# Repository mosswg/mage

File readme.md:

# Mage keyboard (V2 Coming Soon)

# Pictures (with kailh choc robins and MBK Legend Keycaps from [MKUltra Corporation](https://mkultra.click))

## Design principles
 - Resistor grid keyboards are annoying to design and build
 - Finger movement should be reduced as much as possible

## Inspiration
 - MiRage keyboard by Voidstar Labs (Zack Freedman): My motivation for making this
 - Ergodox: Control groups for thumbs
 - Lily58: The basis of the default layout

## Required Materials
 - Seeedstudio Xiao rp2040
 - x4 mcp23017 i/o expander
 - x4 3k Ohm 1204 SMD resistor
 - x4 10k Ohm 1204 SMD resistor
 - x2 3.5mm TRRS Jack
 - TRRS Cable
 - USB-C Cable
 - x64 kaihl choc v1 or v2 switch

## Build guide
1. Solder the R1 and R2 3kOhm resistors
2. Solder the R3 and R4 10kOhm resistors
3. Solder the I/O expanders
4. Solder the Xiao rp2040 on the left half
5. Solder the TRRS Jack
6. Solder on the switches
7. [Program the xiao with the firmware](#program-the-xiao)
8. Write the [default configuration](#default-configuration) and make any [desired modifications](#configuration-modification).
9. Plug everything in and test it
10. [Troubleshoot](#troubleshooting) if needed

## Firmware
#### TODO: Find a better name for the mage firmware
Choose to either use [QMK](#QMK) (more resources and better for beginners) or [mage firmware](#mage-firmware) (more hackable and on the go configuration).

### QMK
Follow the [QMK Getting Started Guide](https://docs.qmk.fm/#/newbs_getting_started) and setup your enviroment. Then, copy `magev2` from this project's `qmk` directory into your `qmk/keyboards/` folder. [Flash the firmware](https://docs.qmk.fm/#/newbs_flashing). The rest of this guide is for the mage firmware. To configure with QMK continue reading their docs.

### Mage Firmware
Initialize the cmake project with `cmake -B build`. Then, build the firmware with `cmake --build build`. Put the microcontroller into bootloader mode by holding the boot button (Labeled 'B' on the xiao) then pressing the reset button (Labeled 'R' on the xiao). Use the `install.sh` script or mount the drive and copy `build/mage_firmware.uf2` to the drive. The configuration must then be written. I recommend using the [default](#default-configuration) at first then changing whatever you see fit.

## Configuration
All configuration is done with the configurator tool. There is a cli and tui interface.
### Building the configurator
Navigate into the configurator folder and run:
```
cmake -B build
cmake --build build
```
The configurator tool will then be in the build folder as 'mage_configurator'.

### Command arguments
Some commands take arguments. For the description of the command required arguments are surrounded by `[]` and optional arguments are surrounded by `<>`. For example:
```
configurator command [required] <optional>
```
Additionally, many commands take an `<index>` argument. This tells the command which config to reference. There are 16 configs to choose from and they can be switch with the CONFIG0-CONFIGF keys.

### Default Configuration
```
configurator default
```
Uploads the default config (defined in `configurator/serial.h`). Does not [save](#Saving-the-config) the config.

### Saving the config
```
configurator save <index>
```
Saves the working config to the given index. If no index is provided saves to the current config index.

### Configuration Modification
```
configurator change [state] [column] [row] [key]
```
Sets the provided state, column, row to the key. All arguments are case insensitive.
State can be "high", "normal", "low", "control" or numbers 0-3 respectively.
Column and row are index numbers. For example, the first column third row (default right arrow) would be referenced with "1 3".
Key is the name of the key that should be at the provided position. This can be the full name or a shortening. For example, The escape key can be "escape" or "ESC". A full list of names is available in the `configurator/keycode.h` file.

```
configurator
```
Opens the working config in the TUI. Each key is interactable and pressing the enter key allow them to take the name of a keycode as input. If the key name is invalid the input will be reverted to the old value and the box will turn red.

### Configuration Restoration
```
configurator restore <index>
```
Pulls from the provided index's config from flash into the working config. The working config will not be saved by this command and the config index is not changed.

### Fetch the config
```
configurator fetch
```
Fetchs the working config from the mage and prints it out.

### Configuration index
```
configurator index <set-index>
```
If `<set-index>` is provided then pull the config at that index and set the current config index to it. Otherwise, prints the current config index.

### File commands
```
configurator download [filename]
```
Saves the current working config as a file with the provided file name.

```
configurator upload [filename]
```
Uploads the config in the file with the provided file name to the mage.

```
configurator edit [filename]
```
Opens the provided file in the TUI and saves to the original file on exit.

## Troubleshooting
### None of the keys are working
Ensure the microcontroller's 5V, Ground, SDA and SCK pins are fully connected and not shorted. There is a normal connection with resistance between the 5V and ground pins but they should not be shorted. Also make sure the microcontroller is working. These 4 pins are the only needed pins on the microcontroller for the mage to work and if any of them are disconnected the entire keyboard will not work.
### A region of keys (16 keys) are not working
This usually means that one of the I/O expanders is not working. Make sure that the 5V, Ground, SDA, and SCK pin are fully connected to the pads on the board.
### A one key/a few keys are not working
This usually means that the keys that aren't working are not connected to the I/O expander. Most often this is because the pin of the I/O expander for that key is not connected properly.

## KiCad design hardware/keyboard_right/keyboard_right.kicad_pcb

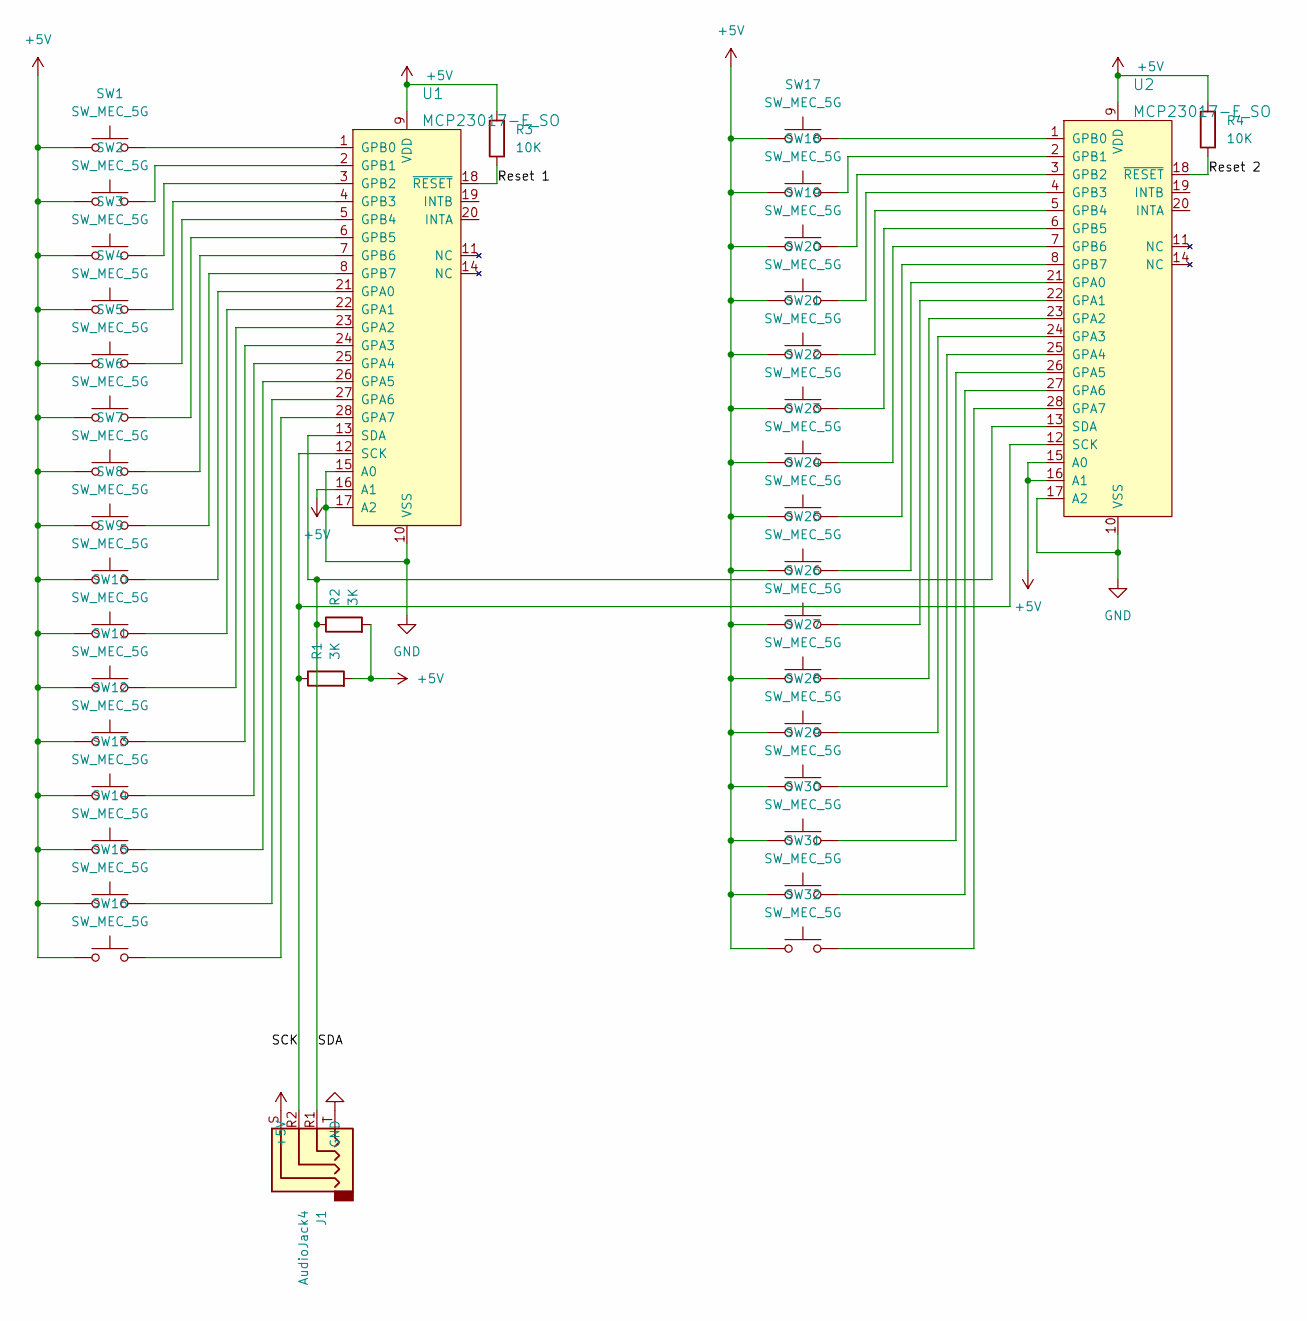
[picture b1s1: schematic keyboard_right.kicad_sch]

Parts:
J1: AudioJack4; Jack_3.5mm_PJ320D_Horizontal
R1, R2: 3K; R_0603_1608Metric_Pad0.98x0.95mm_HandSolder
R3, R4: 10K; R_0603_1608Metric_Pad0.98x0.95mm_HandSolder
SW1, SW2, SW3, SW4, SW5, SW6, SW7, SW8, SW9, SW10, SW11, SW12, SW13, SW14, SW15, SW16, SW17, SW18, SW19, SW20, SW21, SW22, SW23, SW24, SW25, SW26, SW27, SW28, SW31: SW_MEC_5G; SW_Kailh_Choc_V1V2_1.00u
SW29, SW32: SW_MEC_5G; SW_Kailh_Choc_V1V2_1.50u_90deg
SW30: SW_MEC_5G; SW_Kailh_Choc_V1V2_1.50u
U1, U2: MCP23017-E_SO; SOIC-28_W7.5mm; MPN MCP23017-E/SO; Digi-Key_PN MCP23017-E/SO-ND

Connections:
+5V: J1.S, R1.2, R2.2, R3.2, R4.2, SW1.1, SW2.1, SW3.1, SW4.1, SW5.1, SW6.1, SW7.1, SW8.1, SW9.1, SW10.1, SW11.1, SW12.1, SW13.1, SW14.1, SW15.1, SW16.1, SW17.1, SW18.1, SW19.1, SW20.1, SW21.1, SW22.1, SW23.1, SW24.1, SW25.1, SW26.1, SW27.1, SW28.1, SW29.1, SW30.1, SW31.1, SW32.1, U1.9 (VDD), U1.16 (A1), U2.9 (VDD), U2.15 (A0), U2.16 (A1)
/Reset 1: R3.1, U1.18 (~RESET)
/Reset 2: R4.1, U2.18 (~RESET)
/SCK: J1.R2, R1.1, U1.12 (SCK), U2.12 (SCK)
/SDA: J1.R1, R2.1, U1.13 (SDA), U2.13 (SDA)
GND: J1.T, U1.10 (VSS), U1.15 (A0), U1.17 (A2), U2.10 (VSS), U2.17 (A2)
unnamed: SW1.2, U1.1 (GPB0)
unnamed: SW2.2, U1.2 (GPB1)
unnamed: SW3.2, U1.3 (GPB2)
unnamed: SW4.2, U1.4 (GPB3)
unnamed: SW5.2, U1.5 (GPB4)
unnamed: SW6.2, U1.6 (GPB5)
unnamed: SW7.2, U1.7 (GPB6)
unnamed: SW8.2, U1.8 (GPB7)
unnamed: SW9.2, U1.21 (GPA0)
unnamed: SW10.2, U1.22 (GPA1)
unnamed: SW11.2, U1.23 (GPA2)
unnamed: SW12.2, U1.24 (GPA3)
unnamed: SW13.2, U1.25 (GPA4)
unnamed: SW14.2, U1.26 (GPA5)
unnamed: SW15.2, U1.27 (GPA6)
unnamed: SW16.2, U1.28 (GPA7)
unnamed: SW17.2, U2.1 (GPB0)
unnamed: SW18.2, U2.2 (GPB1)
unnamed: SW19.2, U2.3 (GPB2)
unnamed: SW20.2, U2.4 (GPB3)
unnamed: SW21.2, U2.5 (GPB4)
unnamed: SW22.2, U2.6 (GPB5)
unnamed: SW23.2, U2.7 (GPB6)
unnamed: SW24.2, U2.8 (GPB7)
unnamed: SW25.2, U2.21 (GPA0)
unnamed: SW26.2, U2.22 (GPA1)
unnamed: SW27.2, U2.23 (GPA2)
unnamed: SW28.2, U2.24 (GPA3)
unnamed: SW29.2, U2.25 (GPA4)
unnamed: SW30.2, U2.26 (GPA5)
unnamed: SW31.2, U2.27 (GPA6)
unnamed: SW32.2, U2.28 (GPA7)

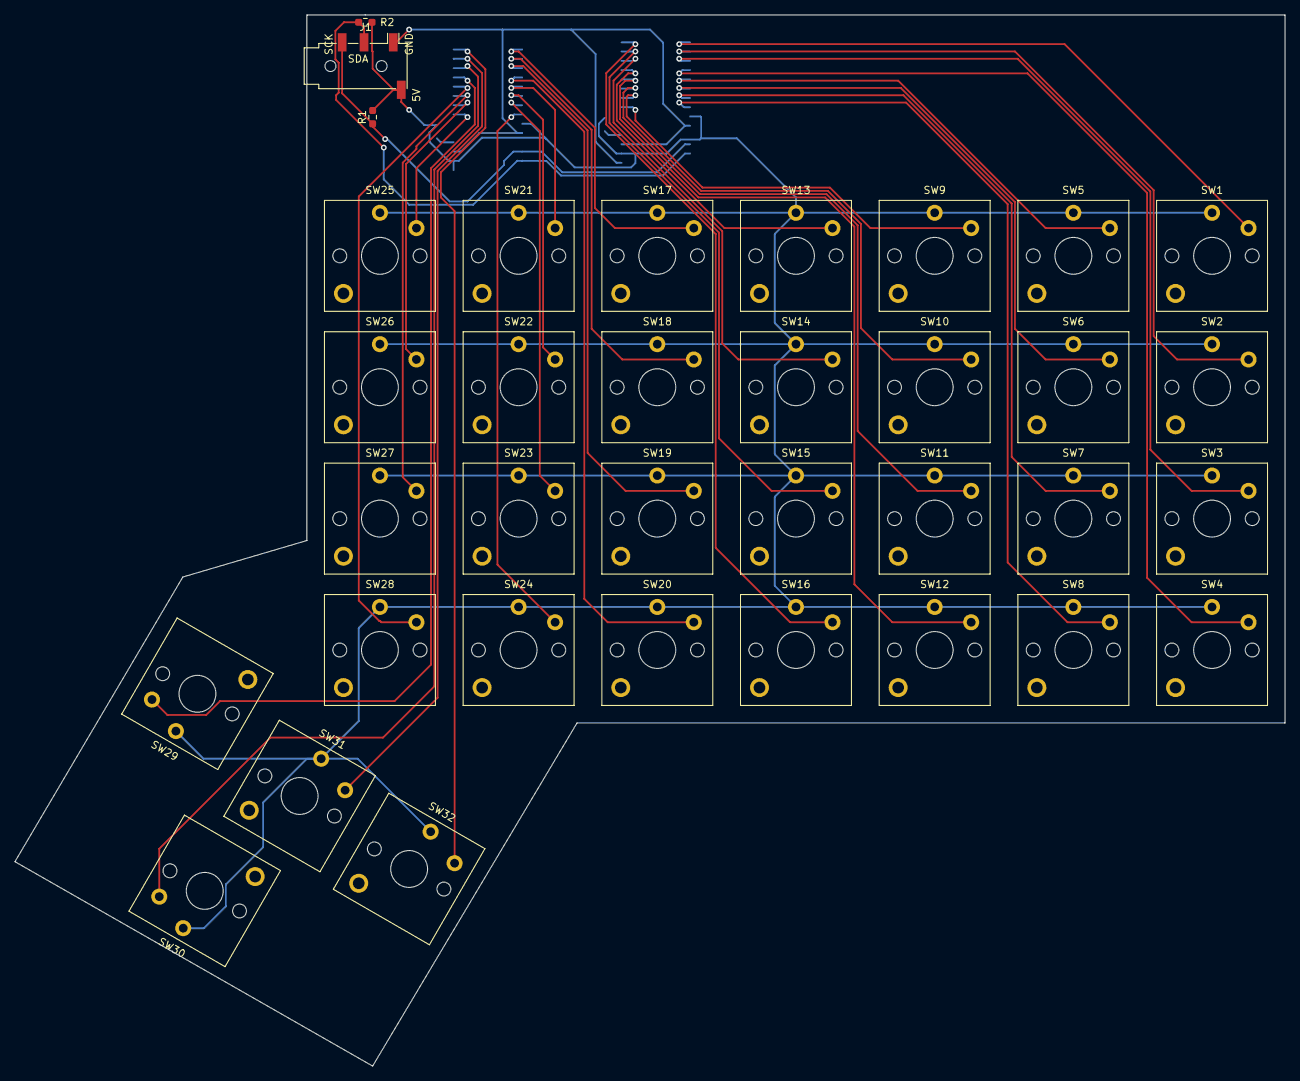
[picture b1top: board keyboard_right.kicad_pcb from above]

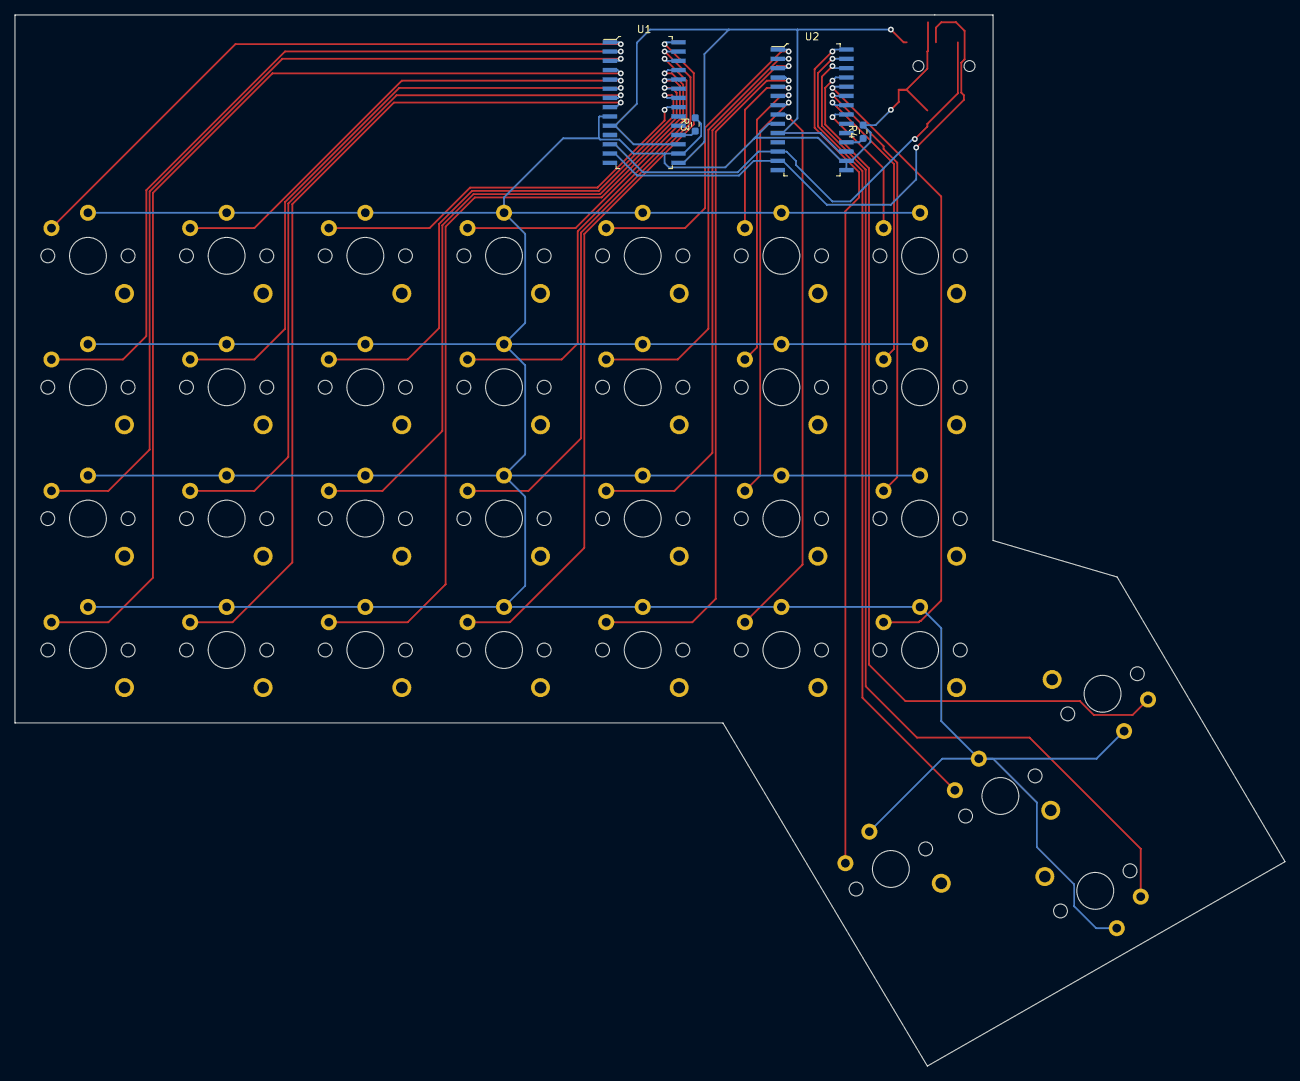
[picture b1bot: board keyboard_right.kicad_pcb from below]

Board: 2 copper layers, 174.0 x 144.0 mm, 39 parts (4 on the bottom side), 38 nets.

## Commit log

2022-12-02 All: Initial Commit
    mcp23017 working with tinyusb with 3 inputs
2022-12-02 Meta: Add License
2023-01-21 Mage Firmware: Finalize V1 Firmware
    I will do bug fixes and such but nothing major. I really happy to be
    typing this commit message on a 100% custom keeb I built. Time to start work on v2.
2023-01-21 Readme: Added Initial Readme for V1
2023-01-22 Readme: Added Pictures of V1
2023-01-22 Readme: Added 'https://' to Image Links
2023-01-22 Readme: Reduced Size of Images
2023-01-22 Readme: Fixed Incorrect Link
2023-05-25 Readme: Fixed Parentheses Around MKUltra Corp
2023-05-25 Config: Start Work On USB Configuration
    Started adding flash storage and serial communication.
2023-05-25 Meta: Making This A Single Repo Instead of Multiple
    Moved firmware files into firmware folder.
2023-05-25 Config: Reworked Config For Upcoming On the Fly Config
    Changed from seperate column arrays to a single array with all keys.
2023-05-25 Configurator: Added Initial Configurator Program
    Eventually this will allow for configuration without reprogramming the
    controller.
2023-05-25 Configuration: Added On The Fly Configuration With Flash Storage
    Using the configurator, the keys can be configured and the configuration
    will persist over reset.
2023-05-26 Readme: Added Note About V2
2023-05-26 MageV2: Added Hardware Files
2023-05-26 MageV1: Added Hardware Files
2023-05-26 MageV2: Fixed Hardware Files
    Accedentially added them as symlinks. Oops...
2023-05-26 MageV1: Fixed Hardware Files
    Accedentially added them as symlinks. Oops, guess you can find out were
    I stored them originally.
2023-05-26 CMake: Fixed Build System
    Something was funky. Now its not. (hopefully)
2023-05-26 Mage: Changed Horrible IO Expander to Physical Position System
    Previously, there was an individual if statement for every possible key
    and a corrisponding secondary check to see if there is room in the
    buffer. Now there is an array and a loop. That's it. Why didn't I do
    this in the first place it was so easy SMH. Anyways the file is now 200
    lines instead of 700 so thats good.
    Also, I fixed a bug that make the keyboard ignore the first key. (Using
2023-05-26 Configurator: Changed Default Back to Normal
2023-05-26 Firmware: Add Safety Check to Ensure Config is in Bounds
    This shouldn't matter when under normal circumstances but, if for any reason 'CFG4' or anything higher was sent over serial it would
    write into to random memory and I don't trust any of you.
2023-05-26 Configurator: Changed from 'doas' to 'sudo' in shell script
2023-05-26 Firmware: Changed to Not Mount, Upload, or Unmount if Build Fails
2023-05-26 Firmware: Changed Debug Output Slightly
2023-05-26 Configurator: Added "CHNG" and "SAVE" commands
    CHNG (change): takes state, column, row, and key. It sets the key the state, column, and row to the specified key.
    SAVE (save): takes nothing. It saves the configuration to flash.
    Without saving the config will not be preserved through loss of power.
2023-05-26 Software Meta: Moved Constants to 'include/mage_const.h'
    This allows the configurator and firmware to use the exact same values.
    Also if anyone want to create something custom they have easy access to
    those values.
2023-05-26 Configurator: Added CLI Argument control
2023-05-26 Configurator: Added Fetch Command
    Fetch gets the current configuration from the keyboard and displays it.
2023-05-26 Configurator: Added Keycode to String Array
    Now you tell what keys you have configured without looking at a giant
    list of keycodes! (yay)
2023-05-26 Configurator: Change Command Responds to Arguments
2023-05-26 Configurator: Added Name to Key Map
2023-05-27 Configurator: Added Non-functional TUI editor to Configurator
    This uses [FTXUI](https://github.com/ArthurSonzogni/FTXUI). This is a
    very cool library but it's some strange design quirks (like hiding
    useful helper functions behind internal files :[ whyyyy). Anyways, it
    works well once you have done some file path haxing (aka '../').
2023-05-27 Configurator: Added TUI Layout Editor
2023-05-28 Readme: Added Info about Configuration
2023-05-28 Configurator: Change Exposing GlyphNext and GlyphPrevious
    Previously importing the "string_internal.hpp" file through path
    traversal. Now just decalare them in the header "key_input.hpp" header
    file.
2023-05-28 Firmware: Added Sleep to Response to Fetch
2023-05-30 MageV2: Added Angled Corners
    45 degree angle with 7mm removed on each edge.
2023-05-30 Configurator: Removed Debug Log Output
2023-05-30 MageV2: Moved Thumb Cluster Key a Few mm
2023-05-30 Configurator: Renamed gridcontainer to grid_container
    This matches with key_input so it just makes sense.
2023-05-30 Configurator: Renamed .hpp to .h
2023-05-30 Configurator: Moved stris to helper.h
    Also created helper.h
2023-05-30 Configurator: Added Config Files
    Configs can now be saved and loaded with files! Yay tech from the 1960s!
2023-05-30 Configurator: Allow Exiting TUI Without CTRL-C
2023-05-31 Configurator: Change tui to Modify Config In Memory
    Previously every change was written to the board as it was made which
    was cool as it was real time. However, It meant that working directly
    with files was impossible so that had to change.
2023-05-31 Firmware: Add MageV2 Left Side IO to Physical Mappings
2023-05-31 MageV2: Moved XIAO to Allow More Space For USB-C
    Also change the silkscreen :>
2023-05-31 Firmware: Move Config Flash Offset to End of Flash
2023-06-01 Firmware: Added Abitily to Have Multiple Configs
2023-06-01 Configurator: Added Ability to Interface with Multiple Configs
2023-06-03 MageV2: Changed Thumb Cluster to be Not Entirely Random
    All angles are multiples of 15 (ish kicad isn't very precise when it
    comes to non-45 degree angle).
2023-06-03 MageV2: Added Resistor Values to Back Silkscreen
2023-06-03 MageV2: Added Updated Gerbers
2023-06-03 Firmware: Fixed MageV2 Thumb Cluster Mappings
    The MageV2 is now verified 100% working. YAY!!!! Feel free to order pcb
    for it although I am still perfecting a few part of the design.
2023-06-05 Firmware: Added QMK Support
    This needs to be tested further but I'm just happy to get some output
    because QMK with i/o expanders sucks. To be fair that's not really what it's
    designed for.
2023-06-05 Firmware: Added CONFIGA-CONFIGF keycodes
2023-06-05 Readme: Updated Configurator Commands
2023-06-05 Configurator: Combined 'index' and 'findex' commands
    Now when no set-index is provided for index it prints the current index
    and exits.
2023-06-05 Configurator: Updated Usage
    Also made a few small modifications to the readme.md.
